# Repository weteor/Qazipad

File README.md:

### Qazipad

unistagger qaz-like w/ numpad

## Features

- MX-Hotswap sockets
- CH552T Controller (w/ FAK firmware), uses japanese duplex matrix
- reversable pcb so you may have numpad right or left
- gerber and case files are supplied (kicad files, stl as well as cadquery files)
- completely open source, permissive license ([CERN-OHL-P](https://cern-ohl.web.cern.ch/home))
- only V2: removeable numpad, more numpad options
  - **V2 pcb is not fully tested yet**

##### layout options

current version in repo (V2):

V1:

not all stab option are tested with the plate. They should work, but maybe there are cases which require some work on the plate.

## Want one?

All production files you need to build your own board can be found [here](./prod/).

Apart from the pcb and optionally a case you need:

- 50 hotswap sockets

- 58 diodes (1N4148 int SOT-123)

- 50 of your favourite switches

- 1x CH552T (TSSOP-20)

- 1x USBLC6-2SC6 (SOT-23-6)

- 1x 10kOhm resistor (SMD 0603)

- 2x 5.1kOhm resistors (SMD 0603)

- 2x 100nF capacitors (SMD 0603)

- 1x USB Connector C-Type, 12 pin/16pin

- 8 M2 heat inserts

- 8 M2 srews (8mm)

### firmware

Config for FAK can be found [here](https://github.com/weteor/fak-config/tree/main/keyboards/qazipad)). Please also see [FAK-Firmware site](https://github.com/semickolon/fak) for more information

Bootloader should be available on plugin until firmware is written. After that either use the firmware BOOT to go into bootloader, or hold the boot button on the pcb pressed while pluggin in the usb cable.

### the rest

Everything in this repository is free to use however you might see fit. If you want to support me and my projects, please consider linking back to this repository if you build/change/use anything.

If you would like to send me a tip, you could do it [here](https://ko-fi.com/weteor) (Please don't feel like you have to).

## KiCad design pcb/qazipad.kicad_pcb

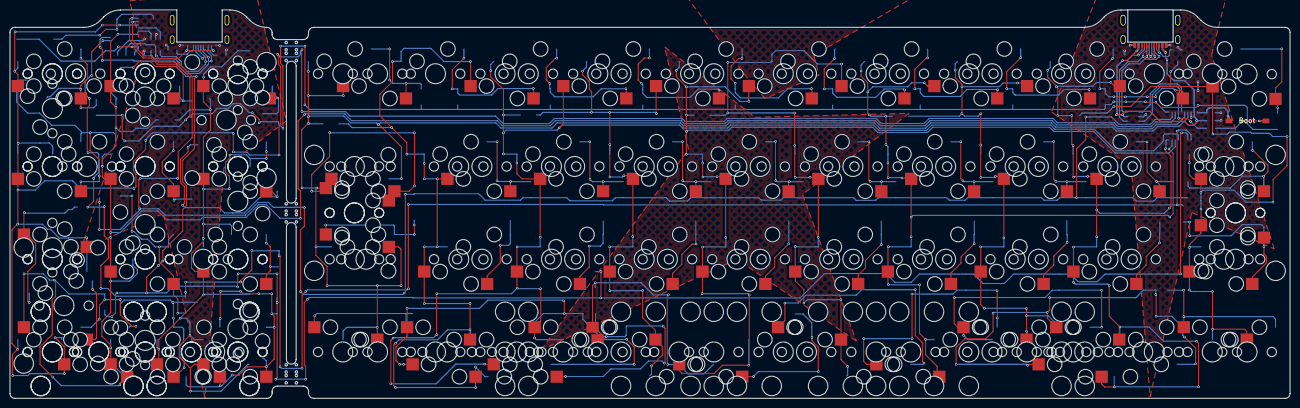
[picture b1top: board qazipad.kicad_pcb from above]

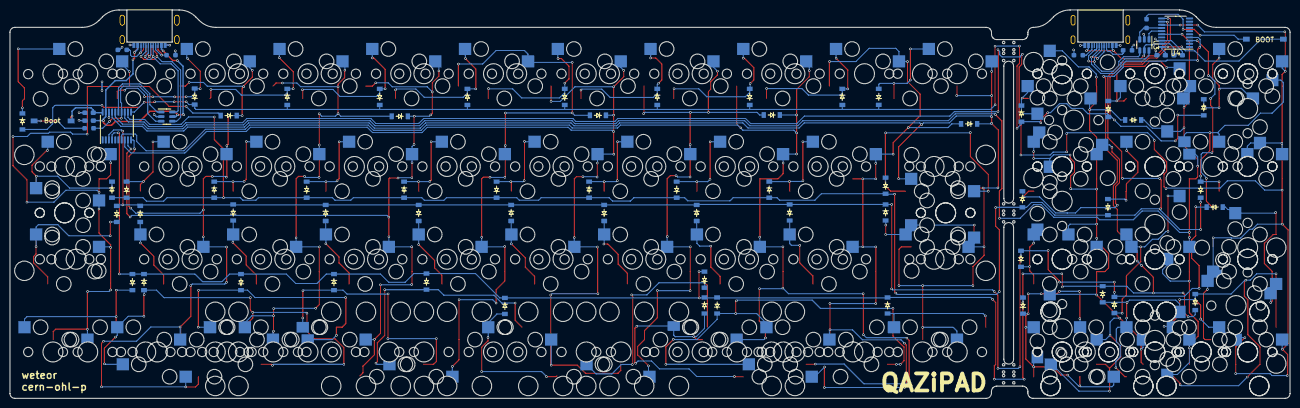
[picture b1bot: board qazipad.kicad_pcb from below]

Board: 2 copper layers, 262.9 x 79.8 mm, 232 parts (148 on the bottom side), 89 nets.

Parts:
C1, C2, C3, C4: 100nF; C_0603_HandSolder
D1, D2, D3, D4, D5, D6, D7, D8, D9, D10, D11, D12, D13, D14, D15, D16, D17, D18, D19, D20, D21, D22, D23, D24, D25, D26, D27, D28, D29, D30, D31, D32, D33, D34, D35, D36, D37, D38, D39, D40, D41, D42, D43, D44, D45, D46, D47, D48, D49, D50, D51, D52, D53, D54, D55, D56, D57, D58: D_Small; D_SOD-123
H1, H2, H3, H4, H5, H6: MouseBites; mousebites_2mm
J1, J2, J3: USB_C_Receptacle_USB2.0; USB-C-12-Pin-MidMount
R1, R2, R4, R5: 5.1k; R_0603_HandSolder
R3, R6: 10k; R_0603_HandSolder
S1, S2, S12, S13, S14, S21: 2u; STAB_MX_P_2u
S3, S4, S8, S10: ISO-Enter; STAB_MX_ISO
S5, S18: 7u; STAB_MX_P_7u
S6, S19: 3u; STAB_MX_P_3u
S7, S16: 2.25u; STAB_MX_P_2.25u
SW1, SW2, SW3, SW6, SW7, SW8, SW10, SW11, SW12, SW15, SW16, SW17, SW18, SW19, SW20, SW21, SW23, SW24, SW25, SW27, SW28, SW29, SW30, SW31, SW32, SW33, SW34, SW35, SW36, SW37, SW38, SW39, SW40, SW43, SW44, SW45, SW47, SW48, SW49, SW51, SW52, SW53, SW55, SW56, SW57, SW58, SW59, SW61, SW63, SW67, SW68, SW71, SW72, SW73, SW75, SW76, SW77, SW80, SW81, SW82, SW83, SW84, SW85, SW86, SW89, SW90, SW91, SW94, SW95, SW96, SW97, SW99, SW100, SW101, SW102, SW103, SW104, SW105, SW106, SW107, SW110, SW111, SW112, SW113, SW115, SW116, SW117, SW119, SW120, SW121, SW122, SW125, SW126, SW127, SW128, SW129, SW131, SW138, SW140: SW_Push; CherryMX_Hotswap_3d_Socketfront
SW4, SW5, SW9, SW13, SW14, SW22, SW26, SW41, SW46, SW50, SW54, SW62, SW66, SW69, SW70, SW74, SW78, SW79, SW87, SW92, SW98, SW109, SW114, SW118, SW123, SW132, SW141: SW_Push; CherryMX_Hotswap_3d
SW42, SW108: BOOT; Micro_Push_Button_3x6x2.5mm
SW60, SW64, SW65, SW88, SW93, SW124: SW_Push; CherryMX_Hotswap_1.25u
SWi: BOOT; Micro_Push_Button_3x6x2.5mm
U1, U3: USBLC6-2SC6; SOT-23-6
U2, U4: TSSOP-20_4.4x6.5mm_P0.65mm

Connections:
+3.3V: C1.1, SW42.2, SW108.2, U2.20 (V33)
+3.3VA: C3.1, SWi.2, U4.20 (V33)
+5VA: C4.1, J2.A4 (VBUS), J2.A9 (VBUS), J2.B4 (VBUS), J2.B9 (VBUS), U3.5 (VBUS), U4.19 (VCC)
BOOT: R3.2, SW42.1, SW108.1
BOOT_NUM: R6.2, SWi.1
CC1: J1.A5 (CC1), J3.B5 (CC2), R1.1
CC1_NUM: J2.A5 (CC1), R4.1
CC2: J1.B5 (CC2), J3.A5 (CC1), R2.1
CC2_NUM: J2.B5 (CC2), R5.1
D1: D1.2 (A), SW1.2, SW39.2, SW61.2
D2: D2.2 (A), SW2.2, SW63.2, SW67.2, SW99.2
D3: D3.2 (A), SW3.2, SW68.2, SW97.1, SW132.1
D4: D4.2 (A), SW19.1, SW20.1, SW21.1, SW22.1, SW60.2, SW84.1, SW85.1, SW86.1, SW87.1, SW88.2
D5: D5.2 (A), SW4.2, SW5.2, SW69.2, SW70.2
D6: D6.2 (A), SW6.1, SW71.2, SW104.2
D7: D7.2 (A), SW7.2, SW72.2
D8: D8.2 (A), SW8.2, SW73.2, SW110.2, SW140.1
D9: D9.2 (A), SW9.2, SW74.2, SW114.2
D10: D10.1 (K), SW10.1, SW75.2, SW119.2
D11: D11.1 (K), SW11.1, SW76.2, SW138.2
D12: D12.1 (K), SW12.2, SW77.2, SW129.2
D13: D13.2 (A), SW27.1, SW28.1, SW29.1, SW41.1, SW62.2, SW94.1, SW95.1, SW96.1
D14: D14.1 (K), SW13.2, SW14.2, SW78.2, SW79.2, SW131.2, SW141.2
D15: D15.2 (A), SW15.2, SW80.2
D16: D16.2 (A), SW16.2, SW31.1, SW81.2
D17: D17.2 (A), SW17.2, SW30.1, SW82.2
D18: D18.2 (A), SW18.2, SW83.2
D19: D19.1 (K), SW19.2, SW84.2
D20: D20.1 (K), SW20.2, SW85.2
D21: D21.1 (K), SW21.2, SW86.2
D22: D22.1 (K), SW22.2, SW60.1, SW87.2, SW88.1
D23: D23.2 (A), SW23.2, SW89.2
D24: D24.2 (A), SW24.2, SW90.2
D25: D25.2 (A), SW25.2, SW91.2
D26: D26.2 (A), SW26.2, SW92.2, SW93.1
D27: D27.1 (K), SW27.2, SW94.2
D28: D28.1 (K), SW28.2, SW95.2
D29: D29.1 (K), SW29.2, SW96.2
D30: D30.2 (A), SW36.1, SW37.1, SW38.1, SW66.2, SW103.1, SW105.1, SW106.1, SW107.1
D31: D31.1 (K), SW41.2, SW62.1
D32: D32.2 (A), SW32.2, SW100.2
D33: D33.2 (A), SW33.2, SW101.2
D34: D34.2 (A), SW34.2, SW102.2
D35: D35.2 (A), SW35.2, SW98.2
D36: D36.1 (K), SW36.2, SW105.2
D37: D37.1 (K), SW37.2, SW106.2
D38: D38.1 (K), SW38.2, SW107.2
D39: D39.2 (A), SW47.1, SW48.1, SW49.1, SW50.1, SW64.2, SW115.1, SW116.1, SW117.1, SW118.1
D40: D40.2 (A), SW40.1, SW55.1, SW56.1, SW57.1, SW58.1, SW59.1, SW125.1, SW126.1, SW127.1, SW128.1
D41: D41.1 (K), SW66.1, SW103.2
D42: D42.2 (A), SW43.2, SW111.2
D43: D43.2 (A), SW44.2, SW112.2
D44: D44.2 (A), SW45.2, SW113.2
D45: D45.2 (A), SW46.2, SW109.1
D46: D46.1 (K), SW47.2, SW115.2
D47: D47.1 (K), SW48.2, SW116.2
D48: D48.1 (K), SW49.2, SW117.2
D49: D49.1 (K), SW50.2, SW64.1, SW118.2
D50: D50.2 (A), SW51.2, SW120.2
D51: D51.2 (A), SW52.2, SW121.2
D52: D52.2 (A), SW53.2, SW122.2
D53: D53.2 (A), SW54.2, SW65.1, SW123.2, SW124.1
D54: D54.1 (K), SW55.2, SW125.2
D55: D55.1 (K), SW56.2, SW59.2, SW126.2
D56: D56.1 (K), SW40.2, SW57.2, SW127.2
D57: D57.1 (K), SW58.2, SW128.2
D58: D58.2 (A), SW10.2, SW11.2, SW12.1, SW13.1, SW14.1, SW75.1, SW76.1, SW77.1, SW78.1, SW79.1, SW119.1, SW129.1, SW131.1, SW138.1, SW140.2, SW141.1
GND: C1.2, C2.2, J1.A1 (GND), J1.A12 (GND), J1.B1 (GND), J1.B12 (GND), J3.A1 (GND), J3.A12 (GND), J3.B1 (GND), J3.B12 (GND), R1.2, R2.2, U1.2 (GND), U2.18 (GND)
GND1: C3.2, C4.2, J2.A1 (GND), J2.A12 (GND), J2.B1 (GND), J2.B12 (GND), R4.2, R5.2, U3.2 (GND), U4.18 (GND)
PORT+: J1.A6 (D+), J1.B6 (D+), J3.A6 (D+), J3.B6 (D+), U1.4 (I/O2)
PORT+_NUM: J2.A6 (D+), J2.B6 (D+), U3.4 (I/O2)
PORT-: J1.A7 (D-), J1.B7 (D-), J3.A7 (D-), J3.B7 (D-), U1.6 (I/O1)
PORT-_NUM: J2.A7 (D-), J2.B7 (D-), U3.6 (I/O1)
UDM: U1.1 (I/O1), U2.15 (P3.7)
UDM_NUM: U3.1 (I/O1), U4.15 (P3.7)
UDP: R3.1, U1.3 (I/O2), U2.14 (P3.6)
UDP_NUM: R6.1, U3.3 (I/O2), U4.14 (P3.6)
VBUS: C2.1, J1.A4 (VBUS), J1.A9 (VBUS), J1.B4 (VBUS), J1.B9 (VBUS), J3.A4 (VBUS), J3.A9 (VBUS), J3.B4 (VBUS), J3.B9 (VBUS), U1.5 (VBUS), U2.19 (VCC)
c1: SW1.1, SW2.1, SW3.1, SW4.1, SW5.1, SW39.1, SW63.1, SW67.1, SW68.1, SW69.1, SW70.1, SW97.2, SW99.1, SW132.2, U2.13 (P3.5), U4.13 (P3.5)
c2: D58.1 (K), SW6.2, SW7.1, SW8.1, SW9.1, SW61.1, SW71.1, SW72.1, SW73.1, SW74.1, SW104.1, SW110.1, SW114.1, U2.16 (P1.3), U4.16 (P1.3)
c3: D4.1 (K), SW15.1, SW16.1, SW17.1, SW18.1, SW30.2, SW31.2, SW80.1, SW81.1, SW82.1, SW83.1, U2.17 (P1.2)
c4: D13.1 (K), SW23.1, SW24.1, SW25.1, SW26.1, SW89.1, SW90.1, SW91.1, SW92.1, SW93.2, U2.7 (P1.0)
c5: D30.1 (K), SW32.1, SW33.1, SW34.1, SW35.1, SW98.1, SW100.1, SW101.1, SW102.1, U2.8 (P1.1)
c6: D39.1 (K), SW43.1, SW44.1, SW45.1, SW46.1, SW109.2, SW111.1, SW112.1, SW113.1, U2.9 (P3.1)
c7: D40.1 (K), SW51.1, SW52.1, SW53.1, SW54.1, SW65.2, SW120.1, SW121.1, SW122.1, SW123.1, SW124.2, U2.10 (P3.0)
r1: D1.1 (K), D6.1 (K), D10.2 (A), D15.1 (K), D19.2 (A), D23.1 (K), D27.2 (A), D32.1 (K), D36.2 (A), D42.1 (K), D46.2 (A), D50.1 (K), D54.2 (A), U2.11 (P3.3), U4.11 (P3.3)
r2: D2.1 (K), D7.1 (K), D11.2 (A), D16.1 (K), D20.2 (A), D24.1 (K), D28.2 (A), D33.1 (K), D37.2 (A), D43.1 (K), D47.2 (A), D51.1 (K), D55.2 (A), U2.12 (P3.4), U4.12 (P3.4)
r3: D3.1 (K), D8.1 (K), D12.2 (A), D17.1 (K), D21.2 (A), D25.1 (K), D29.2 (A), D34.1 (K), D38.2 (A), D44.1 (K), D48.2 (A), D52.1 (K), D56.2 (A), U2.3 (P1.5), U4.3 (P1.5)
r4: D5.1 (K), D9.1 (K), D14.2 (A), D18.1 (K), D22.2 (A), D26.1 (K), D31.2 (A), D35.1 (K), D41.2 (A), D45.1 (K), D49.2 (A), D53.1 (K), D57.2 (A), U2.4 (P1.6), U4.4 (P1.6)

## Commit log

2025-03-15 add pcb
2025-03-15 add case
2025-03-15 add img
2025-03-15 add readme, license
2025-03-15 add prod files
2025-03-15 fix image links in readme
